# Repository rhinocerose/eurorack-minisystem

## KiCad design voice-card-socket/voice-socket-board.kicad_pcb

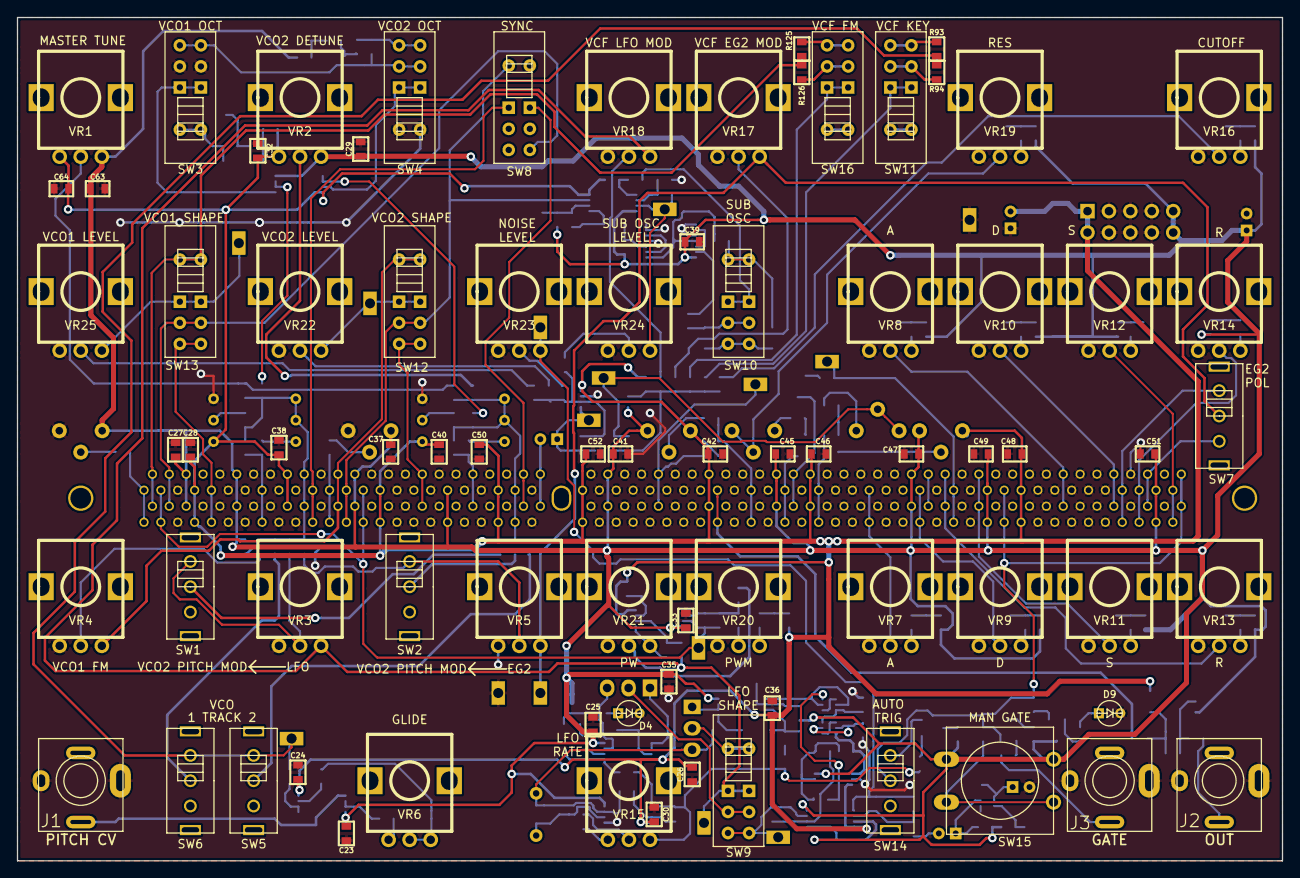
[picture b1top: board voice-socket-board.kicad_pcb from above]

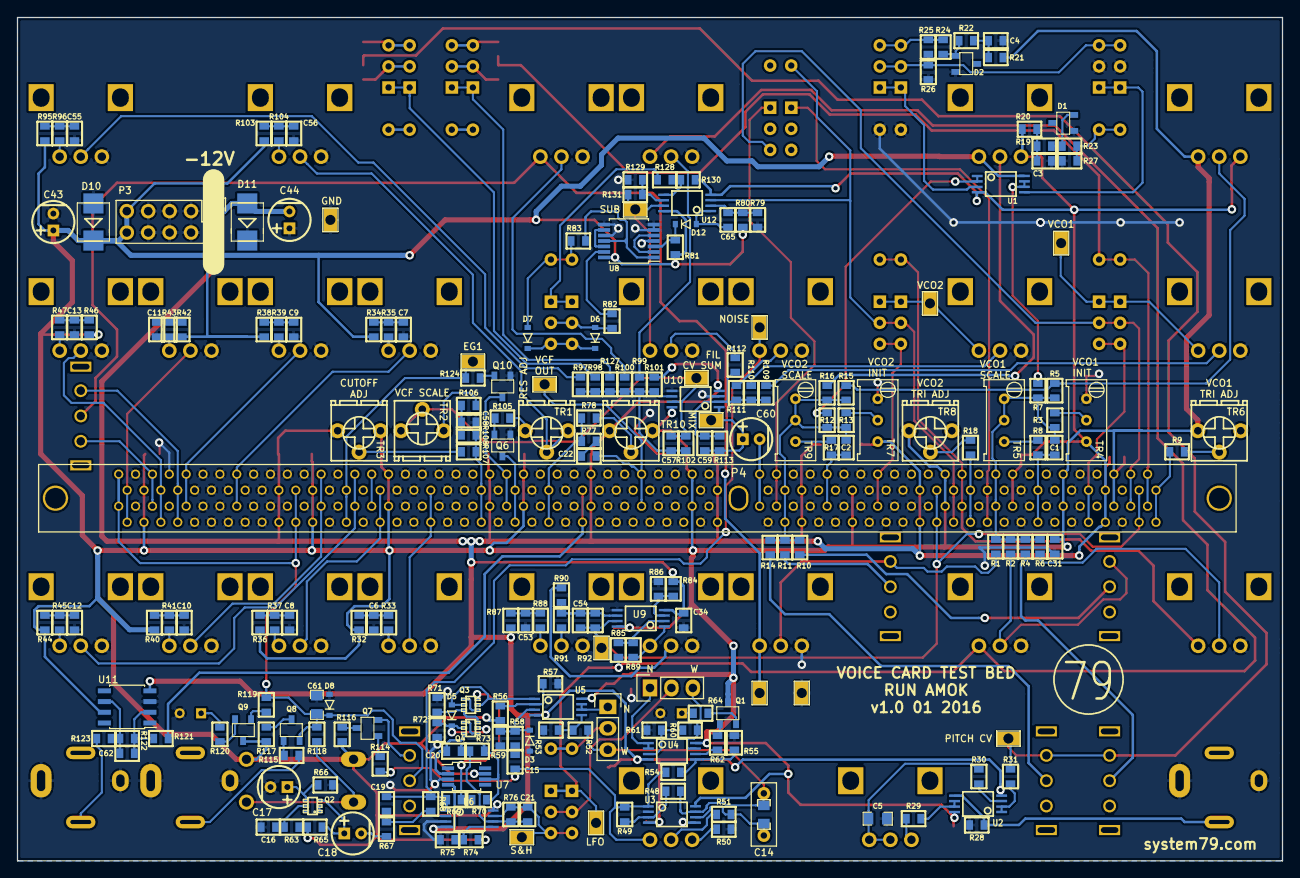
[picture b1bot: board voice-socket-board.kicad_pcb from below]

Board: 2 copper layers, 150.0 x 100.0 mm, 302 parts (224 on the bottom side), 195 nets.

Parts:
C1, C2, C19, C54, C57, C59, C62: 10p; SM0603-C-JRL
C3, C4, C6, C7, C8, C9, C10, C11, C12, C13, C53, C55, C56, C63, C64: 0.1μ; SM0603-C-JRL
C5: 470n; SM0805-HAND
C14: 4.7μ; CAP-5MM-BOX-0805-COMBO
C15, C21: 1n; SM0603-C-JRL
C16, C23, C24, C25, C26, C29, C30, C33, C34, C35, C36, C58: 100n; SM0603-C-JRL
C17, C18: 10μ; 2MM-POL-CAP
C20: 0.01μ; SM0603-C-JRL
C22: 1μ; SM0603-C-JRL
C27, C28, C31, C32, C37, C38, C39, C40, C41, C42, C45, C46, C47, C48, C49, C50, C51, C52: 0.1µ; SM0603-C-JRL
C43, C44: 10μF; 2MM-POL-CAP
C60: 10µ; 2MM-POL-CAP
C61: 220n; SM0805-HAND
C65: 47p; SM0603-C-JRL
D1, D2: LM4040-3.0; SOT23-132-JRL
D3, D5, D6, D7, D8, D12: 1N4148; SOD323-JRL
D4, D9: LED; 3MM-LED-C1A2
D10, D11: D; SMB-1C2A
J1, J2, J3: JACK_MONO_SW; PJ-301B-JACK-SLOTS
P1, P2: CONN_01X03; Pin_Header_Straight_1x03
P3: CONN_02X05; Pin_Header_Straight_2x05
P4: DDR3-DIMM; DDR3-DIMM-240-FCI
Q1, Q7, Q8, Q9: MMBT3904; SOT23-132-JRL
Q2: DMMT3904W; SOT363-JRL
Q3, Q4: 2N7002; SOT363-JRL
Q6, Q10: MMBT3906; SOT23-132-JRL
R1, R2, R3, R4, R6, R7, R10, R11, R12, R13, R14, R56, R68, R76, R77, R85, R89, R90, R91, R92, R97, R98, R99, R100, R102, R109, R110, R111, R112, R127, R129: 100K; SM0603-R-JRL
R5, R15, R16, R78: 2.2meg; SM0603-R-JRL
R8, R17: 91K; SM0603-R-JRL
R9, R18, R28, R71: 1meg; SM0603-R-JRL
R19, R20, R21, R22, R32, R33, R34, R35, R36, R37, R38, R39, R40, R41, R42, R43, R44, R45, R46, R47, R65, R87, R88, R95, R96, R103, R104, R116, R117: 4.7K; SM0603-R-JRL
R23, R59: 20K; SM0603-R-JRL
R24, R25, R26, R27, R30, R54, R55, R57, R114, R115, R118, R119, R121, R122: 10K; SM0603-R-JRL
R29, R31, R50: 100; SM0603-R-JRL
R48, R94, R126: 150K; SM0603-R-JRL
R49: 330K; SM0603-R-JRL
R51, R58, R64, R66, R120, R123: 1K; SM0603-R-JRL
R52, R53, R60, R61, R62, R73, R82, R83, R93, R113, R125, R128: 47K; SM0603-R-JRL
R63: 680K; SM0603-R-JRL
R67, R86: 15K; SM0603-R-JRL
R69, R70: 470; SM0603-R-JRL
R72, R106, R108: 18K; SM0603-R-JRL
R74, R130: 120K; SM0603-R-JRL
R75: 2.7K; SM0603-R-JRL
R79, R80: 220K; SM0603-R-JRL
R81: 68K; SM0603-R-JRL
R84: 56K; SM0603-R-JRL
R101: 390K; SM0603-R-JRL
R105, R124: 27K; SM0603-R-JRL
R107: 680K**; SM0603-R-JRL
R131: 33K; SM0603-R-JRL
SW1, SW2, SW5, SW6, SW14: SPST; SS-12F45-1P2T-SLIDE
SW3, SW4, SW9, SW10, SW11, SW12, SW13, SW16: SP3T; SS-23E02-2P3T-SLIDE
SW7: Switch_SPDT_x2; SS-12F45-1P2T-SLIDE
SW8: 2P3T; SS-23E02-2P3T-SLIDE
SW15: TACT_SWITCH; SW_PUSH-12mm
TP1, TP2, TP3, TP4, TP5, TP6, TP7, TP8, TP9, TP10, TP11, TP12, TP13, TP14, TP15: CONN_1; TEST_POINT_LOOP_4592
TR1, TR2: 20K; Bourns_3362P
TR3, TR6, TR8, TR10: 100K; Bourns_3362P
TR4, TR7: 100K; Bourns-3296W
TR5, TR9: 20K; Bourns-3296W
U1: LM833; TSSOP8-JRL
U2, U3, U4, U5, U6, U9, U10, U12: TL072-; TSSOP8-JRL
U7: MAX9945; MSOP-8_3x3mm_Pitch0.65mm
U8: CD4013; TSSOP-14_4.4x5mm_Pitch0.65mm
U11: NE5534; SOIC-8_3.9x4.9mm_Pitch1.27mm
VR1, VR2, VR3, VR4, VR5, VR7, VR8, VR9, VR10, VR11, VR12, VR13, VR14, VR16, VR17, VR18, VR19, VR20, VR21, VR22, VR23, VR24, VR25: 50K; RV09AF-40-ALPHA-POT
VR6: 1meg LOG; RV09AF-40-ALPHA-POT
VR15: 100K; RV09AF-40-ALPHA-POT

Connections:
+12V: C23.1, C25.1, C27.1, C29.1, C31.1, C33.1, C35.1, C37.1, C39.1, C41.1, C43.1, C45.1, C47.1, C49.1, C51.1, C63.1, D10.1, P3.9, P3.10, P4.6, P4.12, P4.26, P4.37, P4.52, P4.72, P4.88, P4.97, P4.117, P4.126, P4.132, P4.146, P4.157, P4.172, P4.192, P4.208, P4.217, P4.237, Q1.3, Q9.3, R21.1, R32.1, R34.1, R36.1, R38.1, R40.1, R42.1, R44.1, R46.1, R56.2, R63.2, R65.2, R74.2, R80.2, R81.2, R95.1, R103.1, R116.2, R117.2, SW15.1, TR3.1, TR6.3, TR8.3, TR10.1, U1.8, U2.8, U3.8, U4.8, U5.8, U6.8, U7.7, U8.14, U9.8, U10.8, U11.7, U12.8, VR1.3, VR2.3
-12V: C24.2, C26.2, C28.2, C30.2, C32.2, C34.2, C36.2, C38.2, C40.2, C42.2, C44.2, C46.2, C48.2, C50.2, C52.2, C64.2, D11.2, P3.1, P3.2, P4.7, P4.18, P4.29, P4.43, P4.49, P4.64, P4.76, P4.101, P4.127, P4.138, P4.149, P4.163, P4.169, P4.184, P4.196, P4.221, R20.2, R84.1, R87.1, R101.2, R130.2, TR3.3, TR4.3, TR7.3, TR10.3, U1.4, U2.4, U3.4, U4.4, U5.4, U6.4, U7.4, U9.4, U10.4, U11.4, U12.4, VR1.1, VR2.1
EG1_ATTACK_CV: P4.83, P4.203, VR7.2
EG1_DECAY_CV: P4.89, P4.209, VR9.2
EG1_ENV_OUT: P4.93, P4.213, R124.2, TP10.1
EG1_GATE: C61.1, D8.2, P4.99, P4.120, P4.219, P4.240, Q8.2, R118.2, R119.1, SW14.2
EG1_INV_OUT: P4.90, P4.210
EG1_RELEASE_CV: P4.92, P4.212, VR13.2
EG1_SUSTAIN_CV: P4.96, P4.216, VR11.2
EG2_ATTACK_CV: P4.106, P4.226, VR8.2
EG2_DECAY_CV: P4.112, P4.232, VR10.2
EG2_ENV_MOD: R1.2, SW2.1, VR5.2
EG2_ENV_OUT: P4.116, P4.236, SW7.3
EG2_INV_OUT: P4.113, P4.233, SW7.1
EG2_OUT: SW7.2, TP6.1, VR5.3, VR17.3
EG2_RELEASE_CV: P4.115, P4.235, VR14.2
EG2_SUSTAIN_CV: P4.119, P4.239, VR12.2
GND: C3.2, C4.2, C5.2, C6.2, C7.2, C8.2, C9.2, C10.2, C11.2, C12.2, C13.2, C16.1, C17.2, C23.2, C24.1, C25.2, C26.1, C27.2, C28.1, C29.2, C30.1, C31.2, C32.1, C33.2, C34.1, C35.2, C36.1, C37.2, C38.1, C39.2, C40.1, C41.2, C42.1, C43.2, C44.1, C45.2, C46.1, C47.2, C48.1, C49.2, C50.1, C51.2, C52.1, C53.2, C55.2, C56.2, C58.2, C61.2, C63.2, C64.1, D1.1, D2.2, D3.1, D4.1, D8.1, D9.1, D10.2, D11.1, J1.1, J2.1, J3.1, P3.3, P3.4, P3.5, P3.6, P3.7, P3.8, P4.5, P4.8, P4.10, P4.11, P4.13, P4.14, P4.16, P4.17, P4.19, P4.22, P4.28, P4.30, P4.31, P4.32, P4.33, P4.35, P4.36, P4.38, P4.39, P4.41, P4.42, P4.44, P4.47, P4.50, P4.51, P4.53, P4.54, P4.55, P4.56, P4.57, P4.59, P4.60, P4.61, P4.62, P4.63, P4.66, P4.67, P4.68, P4.70, P4.71, P4.75, P4.78, P4.79, P4.80, P4.81, P4.82, P4.84, P4.85, P4.86, P4.87, P4.91, P4.94, P4.95, P4.98, P4.100, P4.102, P4.103, P4.104, P4.105, P4.107, P4.108, P4.109, P4.110, P4.111, P4.114, P4.118, P4.125, P4.128, P4.130, P4.131, P4.133, P4.134, P4.136, P4.137, P4.139, P4.142, P4.148, P4.150, P4.151, P4.152, P4.153, P4.155, P4.156, P4.158, P4.159, P4.161, P4.162, P4.164, P4.167, P4.170, P4.171, P4.173, P4.174, P4.175, P4.176, P4.177, P4.179, P4.180, P4.181, P4.182, P4.183, P4.186, P4.187, P4.188, P4.190, P4.191, P4.195, P4.198, P4.199, P4.200, P4.201, P4.202, P4.204, P4.205, P4.206, P4.207, P4.211, P4.214, P4.215, P4.218, P4.220, P4.222, P4.223, P4.224, P4.225, P4.227, P4.228, P4.229, P4.230, P4.231, P4.234, P4.238, Q6.1, Q10.1, R26.2, R27.1, R28.2, R50.1, R53.2, R55.1, R57.2, R59.2, R61.2, R66.2, R71.2, R72.1, R75.1, R79.2, R86.1, R129.1, SW3.2, SW4.1, TP14.1, TP15.1, TR4.1, TR6.1, TR7.1, TR8.1, U3.2, U3.5, U6.3, U7.3, U8.4, U8.6, U8.7, U8.8, U8.10, U9.5, U10.3, U10.5, U11.3, VR3.1, VR4.1, VR5.1, VR7.1, VR8.1, VR9.1, VR10.1, VR11.1, VR12.1, VR13.1, VR14.1, VR16.1, VR17.1, VR18.1, VR19.1, VR20.1, VR21.1, VR22.1, VR23.1, VR24.1, VR25.1
KEY_TRACK: R31.1, R93.2, R94.1, SW5.1, SW6.1, TP1.1
LFO_GATE: C15.1, R49.1, R54.1, R114.1, U3.1, VR15.3
LFO_MOD: R2.2, SW1.1, VR3.2
LFO_OUT: R85.2, SW9.3, TP12.1, VR3.3, VR18.3
LFO_PULSE: P2.2, SW9.2
LFO_TRI: P1.2, SW9.1
MASTER_TUNE: R5.2, R15.2, VR1.2
NOISE: C19.2, R68.1, R69.2, TP2.1, U6.1, VR23.3
unnamed: C3.1, R19.2, R20.1
unnamed: C4.1, R21.2, R22.1
unnamed: C5.1, R30.2, VR6.2, VR6.3
unnamed: C6.1, R32.2, R33.1
unnamed: C7.1, R34.2, R35.1
unnamed: C8.1, R36.2, R37.1
unnamed: C9.1, R38.2, R39.1
unnamed: C10.1, R40.2, R41.1
unnamed: C11.1, R42.2, R43.1
unnamed: C12.1, R44.2, R45.1
unnamed: C13.1, R46.2, R47.1
unnamed: C14.1, R51.1, U3.6
unnamed: C14.2, P1.3, R48.1, R52.1, U3.7
unnamed: C15.2, R58.1
unnamed: C16.2, Q2.5, R63.1
unnamed: C17.1, Q2.4, R66.1
unnamed: C18.1, Q2.3, R65.1
unnamed: C18.2, R67.2
unnamed: C19.1, R67.1, R68.2, U6.2
unnamed: C20.1, Q4.3, U7.2
unnamed: C20.2, R70.1, R73.2, U7.6
unnamed: C21.1, R73.1, R76.2, U6.6
unnamed: C22.2, R77.2
unnamed: C53.1, R87.2, R88.1
unnamed: C54.1, R90.1, R91.1, R92.2, U9.6
unnamed: C55.1, R95.2, R96.1
unnamed: C56.1, R103.2, R104.1
unnamed: C57.1, R97.1, R98.1, R99.1, R100.1, R101.1, R102.2, R127.1, U10.6
unnamed: C57.2, R102.1, TP4.1, TR2.1, TR2.2, U10.7
unnamed: C58.1, R106.1, R108.2
unnamed: C59.1, C60.1, R113.2, TP5.1, U10.1
unnamed: C59.2, R109.2, R110.2, R111.2, R112.2, R113.1, U10.2
unnamed: C62.1, R121.1, R122.2, U11.2
unnamed: C62.2, R122.1, R123.2, U11.6
unnamed: C65.1, R79.1, R80.1, U12.2
unnamed: C65.2, D12.1, U12.1
unnamed: D1.2, R19.1, R23.2
unnamed: D2.1, R22.2, R24.1
unnamed: D3.2, R58.2, R59.1, U5.3
unnamed: D4.2, R64.2
unnamed: D5.1, Q3.2, Q3.5, U5.1
unnamed: D5.2, Q4.2, Q4.5, R72.2
unnamed: D6.1, R82.2, SW10.2
unnamed: D6.2, D7.2, SW10.4
unnamed: D7.1, R83.2, SW10.1
unnamed: D9.2, R120.2
unnamed: D12.2, R81.1, U8.3
unnamed: J1.3, R28.1, U2.5
unnamed: J2.3, R123.1
unnamed: J3.3, R115.1
unnamed: P1.1, U5.6, U5.7
unnamed: P2.1, U4.1, U4.2
unnamed: P2.3, R60.1, U4.7
unnamed: Q1.1, R62.1
unnamed: Q1.2, R64.1
unnamed: Q2.1, Q2.2
unnamed: Q3.1, Q3.4
unnamed: Q3.3, Q4.6, R71.1
unnamed: Q3.6, R69.1, R70.2
unnamed: Q4.1, Q4.4
unnamed: Q6.2, R105.1
unnamed: Q7.1, R114.2
unnamed: Q7.2, SW14.1
unnamed: Q7.3, R116.1
unnamed: Q8.1, R115.2
unnamed: Q8.3, R117.1
unnamed: Q9.1, R119.2
unnamed: Q9.2, R120.1
unnamed: Q10.2, R124.1
unnamed: R3.2, TR4.2
unnamed: R6.2, VR4.2
unnamed: R8.2, TR5.3
unnamed: R9.2, TR6.2
unnamed: R10.2, SW1.2
unnamed: R11.2, SW2.2
unnamed: R13.2, TR7.2
unnamed: R17.2, TR9.3
unnamed: R18.2, TR8.2
unnamed: R23.1, R27.2, SW3.1
unnamed: R24.2, R25.1, SW4.4
unnamed: R25.2, R26.1, SW3.4, SW4.2
unnamed: R29.1, VR6.1
unnamed: R29.2, U2.6, U2.7
unnamed: R30.1, U2.3
unnamed: R31.2, U2.1, U2.2
unnamed: R33.2, VR7.3
unnamed: R35.2, VR8.3
unnamed: R37.2, VR9.3
unnamed: R39.2, VR10.3
unnamed: R41.2, VR11.3
unnamed: R43.2, VR12.3
unnamed: R45.2, VR13.3
unnamed: R47.2, VR14.3
unnamed: R48.2, R49.2, U3.3
unnamed: R50.2, VR15.1
unnamed: R51.2, VR15.2
unnamed: R52.2, R53.1, U5.5
unnamed: R54.2, R55.2, U4.5
unnamed: R56.1, R57.1, U5.2
unnamed: R60.2, R61.1, U4.3
unnamed: R62.2, U4.6
unnamed: R74.1, R75.2, U6.5
unnamed: R78.1, TR10.2
unnamed: R82.1, U8.13
unnamed: R83.1, U8.1, U8.11
unnamed: R84.2, R86.2, U9.3
unnamed: R85.1, R89.2, U9.2
unnamed: R88.2, VR20.3
unnamed: R89.1, U9.1, VR21.3
unnamed: R90.2, VR21.2
unnamed: R91.2, VR20.2
unnamed: R93.1, SW11.4
unnamed: R94.2, SW11.2
unnamed: R96.2, VR16.3
unnamed: R97.2, VR16.2
unnamed: R98.2, SW11.3
unnamed: R99.2, VR18.2
unnamed: R100.2, VR17.2
unnamed: R104.2, VR19.3
unnamed: R105.2, TR1.3
unnamed: R106.2, TR2.3
unnamed: R107.2, TR3.2
unnamed: R109.1, VR25.2
unnamed: R110.1, VR22.2
unnamed: R111.1, VR23.2
unnamed: R112.1, VR24.2
unnamed: R118.1, SW15.2
unnamed: R125.1, SW16.4
unnamed: R126.2, SW16.2
unnamed: R127.2, SW16.3
unnamed: R128.1, R130.1, U12.5
unnamed: R128.2, SW10.3
unnamed: R129.2, R131.1, U12.6
unnamed: SW3.3, U1.5
unnamed: SW4.3, U1.3
unnamed: SW12.3, TP7.1, VR22.3
unnamed: SW13.3, TP9.1, VR25.3
unnamed: TR1.1, TR1.2, VR19.2
unnamed: U8.2, U8.5
unnamed: U8.9, U8.12
RANDOM: C21.2, R76.1, SW9.4, TP13.1, U6.7
RES_CTRL: P4.73, P4.193, Q6.3
SUB_OSC: R131.2, TP8.1, U12.7, VR24.3
VCA_CTRL: P4.74, P4.194, Q10.3
VCA_IN: P4.69, P4.189, R77.1, R78.2
VCA_OUT: P4.65, P4.185, R121.2
VCF_CTRL: P4.77, P4.197, R107.1, R108.1
VCF_IN: C60.2, P4.48, P4.168
VCF_OUT: C22.1, P4.58, P4.178, TP11.1
VCO1_GLIDE_CV: R4.2, SW6.2
VCO1_OCTAVE: R7.2, U1.6, U1.7
VCO1_PITCH_CV: C1.2, P4.20, P4.140, R1.1, R2.1, R3.1, R4.1, R5.1, R6.1, R7.1, TR5.1, TR5.2
VCO1_PULSE: P4.4, P4.124, SW8.8, SW13.2
VCO1_PWM_CV: C54.2, P4.3, P4.27, P4.123, P4.147, R92.1, TP3.1, U9.7
VCO1_SAW: P4.2, P4.122, R125.2, R126.1, SW13.1
VCO1_SCALE: C1.1, P4.15, P4.135, R8.1
VCO1_SYNC_IN: P4.21, P4.141, SW8.3
VCO1_TRI: P4.9, P4.129, SW13.4
VCO1_TRI_SHAPE: P4.1, P4.121, R9.1
VCO2_GLIDE_CV: R14.2, SW5.2
VCO2_OCTAVE: R12.2, U1.1, U1.2
VCO2_PITCH_CV: C2.2, P4.45, P4.165, R10.1, R11.1, R12.1, R13.1, R14.1, R15.1, R16.1, TR9.1, TR9.2
VCO2_PULSE: P4.25, P4.145, SW8.1, SW12.2, U12.3
VCO2_SAW: P4.24, P4.144, SW12.1, VR4.3
VCO2_SCALE: C2.1, P4.40, P4.160, R17.1
VCO2_SYNC_IN: P4.46, P4.166, SW8.4
VCO2_TRI: P4.34, P4.154, SW12.4
VCO2_TRI_SHAPE: P4.23, P4.143, R18.1
VCO2_TUNE: R16.2, VR2.2

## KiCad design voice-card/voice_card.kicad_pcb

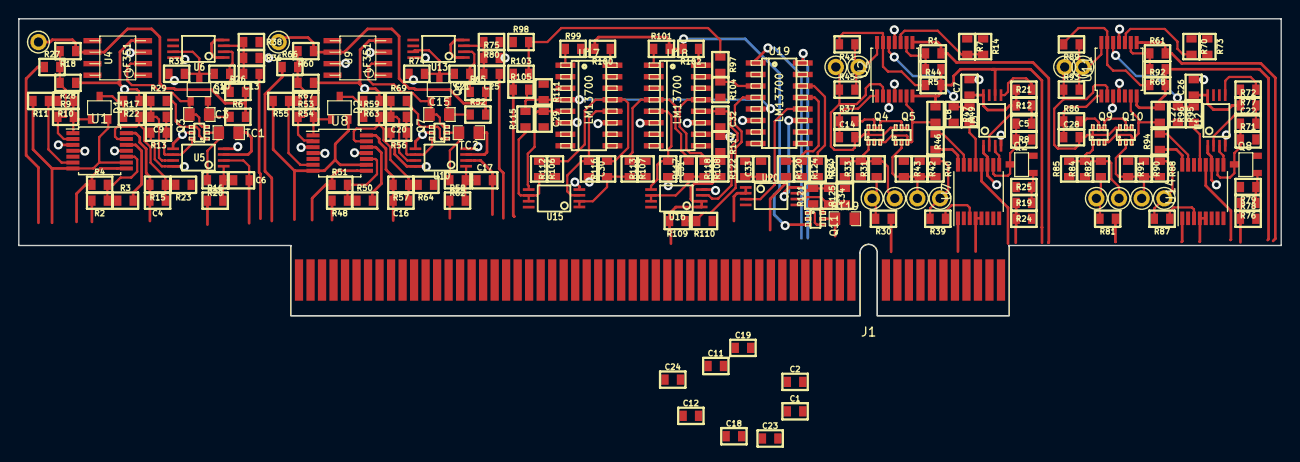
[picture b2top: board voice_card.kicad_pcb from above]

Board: 2 copper layers, 139.3 x 32.8 mm, 207 parts (0 on the bottom side), 141 nets.

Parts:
C1, C2, C5, C7, C11, C12, C18, C19, C22, C23, C24, C26: 100n; SM0603-C-JRL
C3, C15: 2.2n 1%; SM0805-HAND
C4, C6, C9, C13, C14, C16, C17, C20, C25, C28: 100p; SM0603-C-JRL
C8, C27: 100n**; SM0603-C-JRL
C10, C21: 18p; SM0603-C-JRL
C29, C30, C31, C32: 270pF; SM0603-C-JRL
C33, C34: 47pF; SM0603-C-JRL
D1, D2: BAV70; SOT23-JRL
J1: PCI_11_49; PCI-49-11-CARD-EDGE
Q1, Q6: MMBF4391LT1G; SOT23-JRL
Q2, Q8: 2N3904; SOT23-JRL
Q3, Q7: BCM847; SOT363-JRL
Q4, Q9: DMMT3904; SOT363-JRL
Q5, Q10: DMMT3906; SOT363-JRL
Q11: BC857BS; SOT363-JRL
R1, R5, R24, R61, R68, R78, R97, R109: 100K; SM0603-R-JRL
R2, R7, R12, R14, R18, R29, R38, R48, R60, R69, R70, R72, R73, R80, R98: 10K; SM0603-R-JRL
R3, R10, R11, R20, R23, R28, R50, R54, R55, R62, R64, R67: 56K; SM0603-R-JRL
R4, R27, R51, R66: 1M; SM0603-R-JRL
R6, R52: 680; SM0603-R-JRL
R8, R71: 22K; SM0603-R-JRL
R9, R53: 39K; SM0603-R-JRL
R13, R56, R125: 1.5M; SM0603-R-JRL
R15, R19, R57, R76: 33K; SM0603-R-JRL
R16, R58: 91K; SM0603-R-JRL
R17, R22, R26, R46, R59, R63, R65, R94: 15K; SM0603-R-JRL
R21, R77: 3.3K**; SM0603-R-JRL
R25, R79: 330K; SM0603-R-JRL
R30, R39, R81, R87: 82K*; SM0603-R-JRL
R31, R40, R82, R88, R120: 4.7K; SM0603-R-JRL
R33, R37, R42, R84, R86, R90: 2.2K; SM0603-R-JRL
R34, R43, R85, R91: 270K; SM0603-R-JRL
R35, R74: 3.3K; SM0603-R-JRL
R36, R75: 20K; SM0603-R-JRL
R41, R44, R47, R49, R89, R92, R95, R96, R122: 47K; SM0603-R-JRL
R45, R93, R103, R105: 150K; SM0603-R-JRL
R99, R100, R101, R102: 18K; SM0603-R-JRL
R104, R110, R121: 1.5K; SM0603-R-JRL
R106, R107, R108, R115, R116, R117, R118: 68K; SM0603-R-JRL
R111, R112, R113, R114, R123, R124: 560; SM0603-R-JRL
R119: 1K 3300 ppm/K; SM0805-HAND
TC1, TC2: 1K 3300ppm/K; SM0805-HAND
TP1, TP2, TP3, TP4, TP5, TP6, TP7, TP8, TP9, TP10, TP11, TP12, TP13, TP14: TEST_POINT; TEST_POINT_5000_SERIES
U1, U2, U8, U11: TL074-; TSSOP-14_4.4x5mm_Pitch0.65mm
U3, U12: NE555; TSSOP8-JRL
U4, U9: LF351; so-8
U5, U10, U15, U16, U20: TL072-; TSSOP8-JRL
U6, U13: LM311M; TSSOP8-JRL
U7, U14: CD4052; TSSOP-16_4.4x5mm_Pitch0.65mm
U17, U18, U19: LM13700; SO16-JRL

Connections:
+12V: C1.1, C7.1, C11.1, C18.1, C23.1, C26.1, J1.A1, J1.A13, J1.A25, J1.A36, J1.A47, J1.B1, J1.B13, J1.B25, J1.B36, J1.B47, R8.2, R12.1, R13.2, R14.1, R21.2, R36.2, R46.1, R56.2, R71.2, R72.1, R73.1, R75.2, R77.2, R94.1, U1.4, U2.4, U3.4, U3.8, U4.7, U5.8, U6.8, U7.16, U8.4, U9.7, U10.8, U11.4, U12.4, U12.8, U13.8, U14.16, U15.8, U16.8, U17.11, U18.11, U19.11, U20.8
-12V: C2.2, C12.2, C19.2, C24.2, J1.A3, J1.A15, J1.A27, J1.A38, J1.A49, J1.B3, J1.B15, J1.B27, J1.B38, J1.B49, R22.1, R23.1, R25.2, R28.1, R34.1, R43.1, R63.1, R64.1, R67.1, R79.2, R85.1, R91.1, R125.2, U1.11, U2.11, U4.4, U5.4, U6.1, U6.4, U8.11, U9.4, U10.4, U11.11, U13.1, U13.4, U15.4, U16.4, U17.6, U18.6, U19.6, U20.4
EG1_ATTACK_CV: J1.A39, J1.B39, R30.1
EG1_DECAY_CV: J1.A40, J1.B40, U7.1
EG1_ENV_OUT: C8.1, J1.A45, J1.B45, R5.1, R44.2, U2.7, U3.6
EG1_GATE: J1.A44, J1.B44, R19.2, R24.1
EG1_INV_OUT: J1.A46, J1.B46, R1.2, U2.8
EG1_RELEASE_CV: J1.A42, J1.B42, U7.4, U7.5
EG1_SUSTAIN_CV: J1.A41, J1.B41, U7.12
EG2_ATTACK_CV: J1.A50, J1.B50, R81.1
EG2_DECAY_CV: J1.A51, J1.B51, U14.1
EG2_ENV_OUT: C27.1, J1.A56, J1.B56, R68.1, R92.2, U11.7, U12.6
EG2_GATE: J1.A55, J1.B55, R76.2, R78.1
EG2_INV_OUT: J1.A57, J1.B57, R61.2, U11.8
EG2_RELEASE_CV: J1.A53, J1.B53, U14.4, U14.5
EG2_SUSTAIN_CV: J1.A52, J1.B52, U14.12
GND: C1.2, C2.1, C7.2, C11.2, C12.1, C18.2, C19.1, C23.2, C24.1, C26.2, C29.2, C30.2, C31.2, C32.2, C33.2, J1.A2, J1.A8, J1.A14, J1.A20, J1.A26, J1.A32, J1.A37, J1.A43, J1.A48, J1.A54, J1.A58, J1.A59, J1.A60, J1.B2, J1.B8, J1.B14, J1.B20, J1.B26, J1.B32, J1.B37, J1.B43, J1.B48, J1.B54, J1.B58, J1.B59, J1.B60, Q2.1, Q3.5, Q4.2, Q5.1, Q7.5, Q8.1, Q9.2, Q10.1, Q11.2, R3.2, R7.1, R24.2, R33.1, R35.1, R38.1, R42.1, R47.2, R50.2, R70.1, R74.1, R78.2, R80.1, R84.1, R90.1, R95.2, R98.1, R104.2, R110.1, R111.1, R112.1, R113.1, R114.1, R119.2, R122.2, R123.2, R124.2, TC1.1, TC2.1, U1.3, U1.5, U1.12, U2.3, U2.5, U3.1, U4.3, U5.3, U5.5, U7.2, U7.6, U7.7, U7.8, U7.11, U7.14, U8.3, U8.5, U8.12, U9.3, U10.3, U10.5, U11.3, U11.5, U12.1, U14.2, U14.6, U14.7, U14.8, U14.11, U14.14, U17.3, U17.14, U18.3, U18.14, U20.5
Iabc: Q11.3, R99.2, R100.2, R101.2, R102.2
unnamed: C3.1, Q1.2, Q3.3, U4.2
unnamed: C3.2, Q1.1, R6.1
unnamed: C4.1, R15.1, R17.2, R23.2, U1.13
unnamed: C5.1, Q2.3, R8.1, U7.10
unnamed: C5.2, R12.2, U3.2
unnamed: C6.1, R16.2, R20.1, U5.1
unnamed: C8.2, Q4.3, Q5.3, U2.6
unnamed: C9.1, Q3.6, R13.1, U5.6
unnamed: C9.2, R29.1, U5.7
unnamed: C10.1, R26.1, U6.2
unnamed: C10.2, Q1.3, R35.2, U6.7
unnamed: C13.2, R36.1, R38.2, U6.3
unnamed: C14.1, R37.1, U2.1
unnamed: C14.2, Q4.6, Q5.6, R45.1, TP6.1, U2.2
unnamed: C15.1, Q6.2, Q7.3, U9.2
unnamed: C15.2, Q6.1, R52.1
unnamed: C16.1, R57.1, R59.2, R64.2, U8.13
unnamed: C17.1, R58.2, R62.1, U10.1
unnamed: C20.1, Q7.6, R56.1, U10.6
unnamed: C20.2, R69.1, U10.7
unnamed: C21.1, R65.1, U13.2
unnamed: C21.2, Q6.3, R74.2, U13.7
unnamed: C22.1, Q8.3, R71.1, U14.10
unnamed: C22.2, R72.2, U12.2
unnamed: C25.2, R75.1, R80.2, U13.3
unnamed: C27.2, Q9.3, Q10.3, U11.6
unnamed: C28.1, R86.1, U11.1
unnamed: C28.2, Q9.6, Q10.6, R93.1, TP13.1, U11.2
unnamed: C29.1, U15.5, U17.5
unnamed: C30.1, U15.3, U17.12
unnamed: C31.1, U16.5, U18.5
unnamed: C32.1, U16.3, U18.12
unnamed: C33.1, R122.1, U19.12, U20.3
unnamed: C34.1, R121.2, U20.7
unnamed: C34.2, Q11.6, R125.1, U20.6
unnamed: D1.2, R9.2, R10.1, U1.1
unnamed: D1.3, R17.1, R22.2
unnamed: D2.2, R53.2, R54.1, U8.1
unnamed: D2.3, R59.1, R63.2
unnamed: Q2.2, R19.1, R25.1
unnamed: Q3.1, Q3.4, R29.2
unnamed: Q3.2, R20.2, TC1.2
unnamed: Q4.1, R31.2, R33.2, R34.2, TP3.1
unnamed: Q4.4, Q4.5, Q5.4, Q5.5, R37.2
unnamed: Q5.2, R40.2, R42.2, R43.2, TP5.1
unnamed: Q7.1, Q7.4, R69.2
unnamed: Q7.2, R62.2, TC2.2
unnamed: Q8.2, R76.1, R79.1
unnamed: Q9.1, R82.2, R84.2, R85.2, TP10.1
unnamed: Q10.2, R88.2, R90.2, R91.2, TP12.1
unnamed: Q9.4, Q9.5, Q10.4, Q10.5, R86.2
unnamed: Q11.1, Q11.4, R121.1
unnamed: R1.1, R5.2, U2.9
unnamed: R2.1, R3.1, R4.2, U1.10
unnamed: R10.2, R11.1, U1.6
unnamed: R7.2, R14.2, U2.10
unnamed: R6.2, R18.1, R26.2, TP1.1, U4.6
unnamed: R9.1, R18.2, R27.2, R28.2, U1.2
unnamed: R21.1, U3.5
unnamed: R30.2, R31.1, TP2.1
unnamed: R39.1, U7.3
unnamed: R39.2, R40.1, TP4.1
unnamed: R41.1, R45.2, TP7.1, U2.14
unnamed: R41.2, R44.1, U2.13
unnamed: R46.2, U7.15
unnamed: R47.1, R49.2, U2.12
unnamed: R48.1, R50.1, R51.2, U8.10
unnamed: R49.1, U7.13
unnamed: R52.2, R60.1, R65.2, TP8.1, U9.6
unnamed: R53.1, R60.2, R66.2, R67.2, U8.2
unnamed: R54.2, R55.1, U8.6
unnamed: R61.1, R68.2, U11.9
unnamed: R70.2, R73.2, U11.10
unnamed: R77.1, U12.5
unnamed: R81.2, R82.1, TP9.1
unnamed: R87.1, U14.3
unnamed: R87.2, R88.1, TP11.1
unnamed: R89.1, R93.2, TP14.1, U11.14
unnamed: R89.2, R92.1, U11.13
unnamed: R94.2, U14.15
unnamed: R95.1, R96.2, U11.12
unnamed: R96.1, U14.13
unnamed: R99.1, U17.1
unnamed: R100.1, U17.16
unnamed: R101.1, U18.1
unnamed: R102.1, U18.16
unnamed: R97.1, R98.2, R103.2
unnamed: R97.2, R104.1, U19.3
unnamed: R105.2, R111.2, R115.2, U17.4, U19.5
unnamed: R106.1, R112.2, R116.2, U17.13
unnamed: R106.2, R115.1, U15.6, U15.7
unnamed: R107.1, R113.2, R117.2, U18.4
unnamed: R107.2, R116.1, U15.1, U15.2
unnamed: R108.1, R114.2, R118.2, U18.13
unnamed: R108.2, R117.1, U16.6, U16.7
unnamed: R109.1, R110.2, U19.4
unnamed: R120.1, R124.1, U19.13
unnamed: R123.1, U19.14
unnamed: U3.3, U7.9
unnamed: U12.3, U14.9
RES_CTRL: J1.A30, J1.B30, U19.1
VCA_CTRL: J1.A31, J1.B31, U19.16
VCA_IN: J1.A34, J1.B34, R120.2
VCA_OUT: J1.A35, J1.B35, U20.1, U20.2
VCF_CTRL: J1.A29, J1.B29, Q11.5, R119.1
VCF_IN: J1.A28, J1.B28, R103.1, R105.1
VCF_OUT: J1.A33, J1.B33, R109.2, R118.1, U16.1, U16.2
VCO1_PITCH_CV: C6.2, J1.A7, J1.B7, U5.2
VCO1_PULSE: J1.A12, J1.B12, R4.1, U1.8
VCO1_PWM_CV: J1.A6, J1.B6, R2.2
VCO1_SAW: D1.1, J1.A11, J1.B11, R11.2, U1.7, U1.9
VCO1_SCALE: J1.A9, J1.B9, R16.1
VCO1_SYNC_IN: C13.1, J1.A5, J1.B5
VCO1_TRI: C4.2, J1.A10, J1.B10, R15.2, U1.14
VCO1_TRI_SHAPE: J1.A4, J1.B4, R27.1
VCO2_PITCH_CV: C17.2, J1.A19, J1.B19, U10.2
VCO2_PULSE: J1.A24, J1.B24, R51.1, U8.8
VCO2_PWM_CV: J1.A18, J1.B18, R48.2
VCO2_SAW: D2.1, J1.A23, J1.B23, R55.2, U8.7, U8.9
VCO2_SCALE: J1.A21, J1.B21, R58.1
VCO2_SYNC_IN: C25.1, J1.A17, J1.B17
VCO2_TRI: C16.2, J1.A22, J1.B22, R57.2, U8.14
VCO2_TRI_SHAPE: J1.A16, J1.B16, R66.1

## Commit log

2022-02-03 Added all minisystem repos
2022-04-25 Removed some git files
2025-08-03 Added submodules
2025-08-12 Added
2025-08-13 Remove .gitmodules (no submodules exist)
